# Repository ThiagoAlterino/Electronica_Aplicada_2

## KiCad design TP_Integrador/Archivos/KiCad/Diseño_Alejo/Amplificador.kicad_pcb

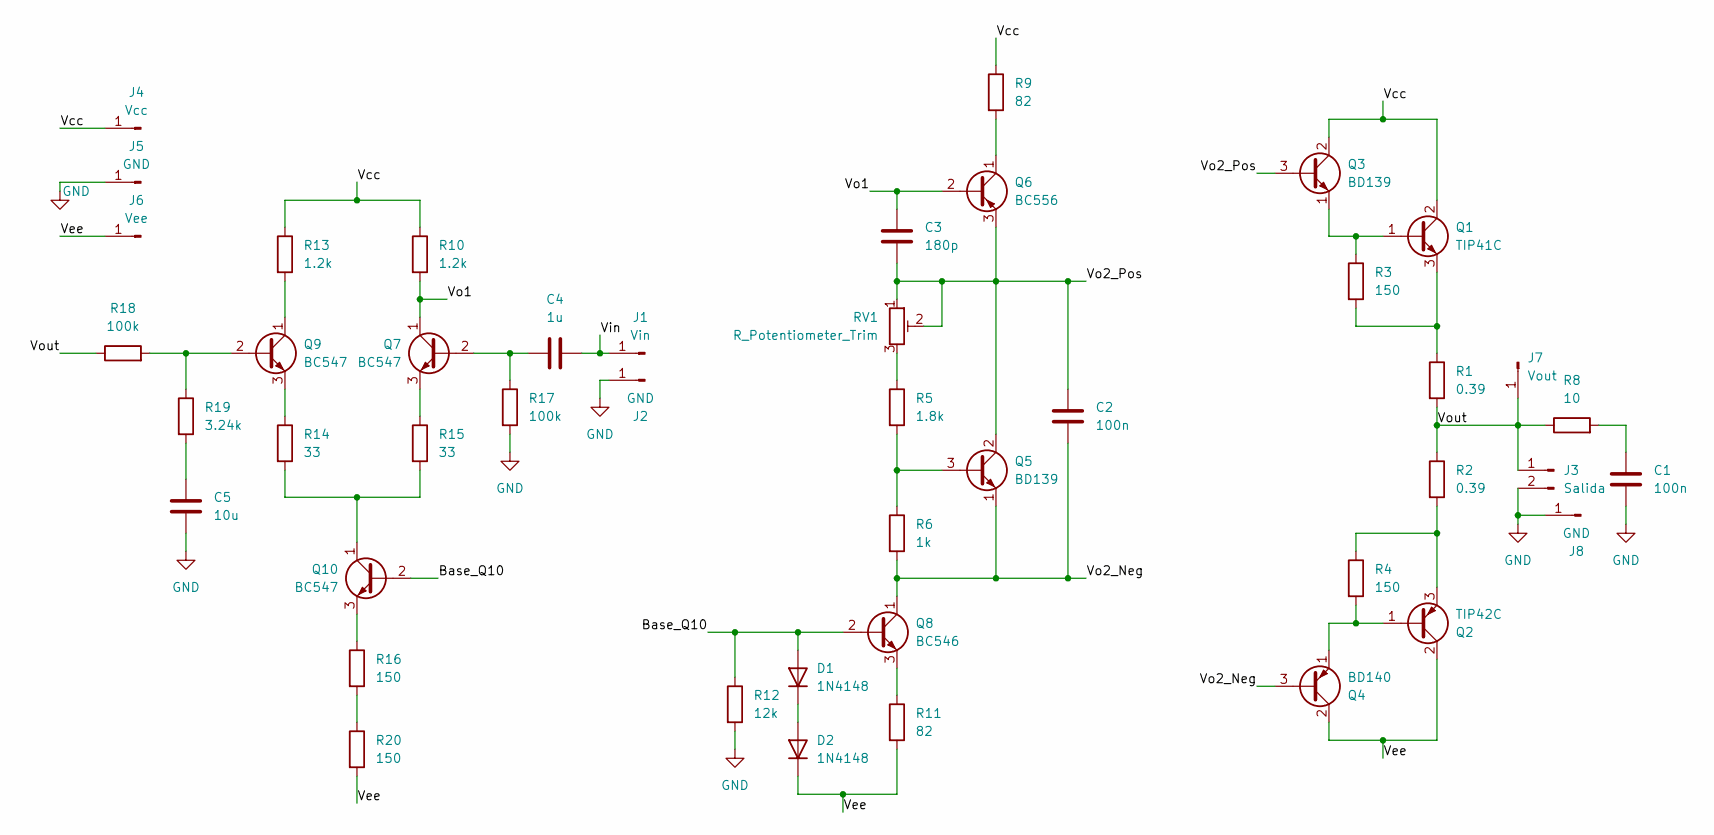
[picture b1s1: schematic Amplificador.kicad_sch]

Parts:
C1, C2: 100n; C_Rect_L7.2mm_W2.5mm_P5.00mm_FKS2_FKP2_MKS2_MKP2
C3: 180p; C_Disc_D5.0mm_W2.5mm_P5.00mm
C4: 1u; C_Rect_L10.3mm_W5.0mm_P7.50mm_MKS4
C5: 10u; CP_Radial_D5.0mm_P2.50mm
D1, D2: 1N4148; D_DO-35_SOD27_P7.62mm_Horizontal
J1: Vin; PinHeader_1x01_P2.54mm_Vertical
J2, J5, J8: GND; PinHeader_1x01_P2.54mm_Vertical
J3: Salida; TerminalBlock_Phoenix_MKDS-1,5-2-5.08_1x02_P5.08mm_Horizont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
J4: Vcc; PinHeader_1x01_P2.54mm_Vertical
J6: Vee; PinHeader_1x01_P2.54mm_Vertical
J7: Vout; PinHeader_1x01_P2.54mm_Vertical
Q1: TIP41C; TO-220-3_Vertical
Q2: TIP42C; TO-220-3_Vertical
Q3, Q5: BD139; TO-126-3_Vertical
Q4: BD140; TO-126-3_Vertical
Q6: BC556; TO-92_Inline
Q7, Q9, Q10: BC547; TO-92_Inline
Q8: BC546; TO-92_Inline
R1, R2: 0.39; R_Axial_DIN0414_L11.9mm_D4.5mm_P15.24mm_Horizontal
R3, R4, R16, R20: 150; R_Axial_DIN0207_L6.3mm_D2.5mm_P10.16mm_Horizontal
R5: 1.8k; R_Axial_DIN0207_L6.3mm_D2.5mm_P10.16mm_Horizontal
R6: 1k; R_Axial_DIN0207_L6.3mm_D2.5mm_P10.16mm_Horizontal
R8: 10; R_Axial_DIN0309_L9.0mm_D3.2mm_P12.70mm_Horizontal
R9, R11: 82; R_Axial_DIN0207_L6.3mm_D2.5mm_P10.16mm_Horizontal
R10, R13: 1.2k; R_Axial_DIN0207_L6.3mm_D2.5mm_P10.16mm_Horizontal
R12: 12k; R_Axial_DIN0207_L6.3mm_D2.5mm_P10.16mm_Horizontal
R14, R15: 33; R_Axial_DIN0207_L6.3mm_D2.5mm_P10.16mm_Horizontal
R17, R18: 100k; R_Axial_DIN0207_L6.3mm_D2.5mm_P10.16mm_Horizontal
R19: 3.24k; R_Axial_DIN0207_L6.3mm_D2.5mm_P10.16mm_Horizontal
RV1: R_Potentiometer_Trim; Potentiometer_Bourns_3296W_Vertical

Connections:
/Base_Q10: D1.2 (A), Q8.2 (B), Q10.2 (B), R12.1
/Vcc: J4.1 (Pin_1_1), Q1.2 (C), Q3.2 (C), R9.1, R10.1, R13.1
/Vee: D2.1 (K), J6.1 (Pin_1_1), Q2.2 (C), Q4.2 (C), R11.2, R20.2
/Vin: C4.2, J1.1 (Pin_1_1)
/Vo1: C3.1, Q6.2 (B), Q7.1 (C), R10.2
/Vo2_Neg: C2.2, Q4.3 (B), Q5.1 (E), Q8.1 (C), R6.2
/Vo2_Pos: C2.1, C3.2, Q3.3 (B), Q5.2 (C), Q6.3 (E), RV1.1, RV1.2
/Vout: J3.1, J7.1 (Pin_1_1), R1.2, R2.1, R8.1, R18.1
GND: C1.2, C5.2, J2.1 (Pin_1_1), J3.2, J5.1 (Pin_1_1), J8.1 (Pin_1_1), R12.2, R17.2
unnamed: C1.1, R8.2
unnamed: C5.1, R19.2
unnamed: D1.1 (K), D2.2 (A)
unnamed: Q1.1 (B), Q3.1 (E), R3.1
unnamed: Q1.3 (E), R1.1, R3.2
unnamed: Q2.1 (B), Q4.1 (E), R4.2
unnamed: Q2.3 (E), R2.2, R4.1
unnamed: Q5.3 (B), R5.2, R6.1
unnamed: Q6.1 (C), R9.2
unnamed: C4.1, Q7.2 (B), R17.1
unnamed: Q7.3 (E), R15.1
unnamed: Q8.3 (E), R11.1
unnamed: Q9.2 (B), R18.2, R19.1
unnamed: Q9.1 (C), R13.2
unnamed: Q9.3 (E), R14.1
unnamed: Q10.1 (C), R14.2, R15.2
unnamed: Q10.3 (E), R16.1
unnamed: R5.1, RV1.3
unnamed: R16.2, R20.1

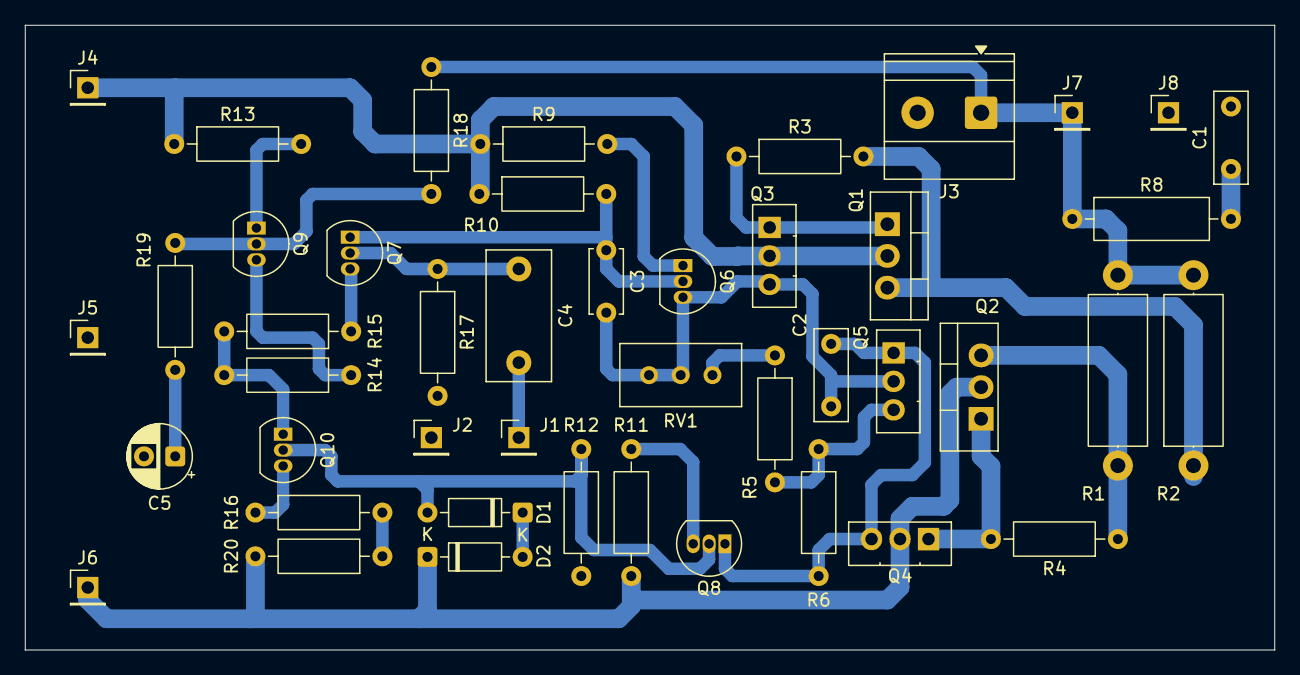
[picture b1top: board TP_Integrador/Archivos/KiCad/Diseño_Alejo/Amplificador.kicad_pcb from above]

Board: 2 copper layers, 100.0 x 50.0 mm, 45 parts (0 on the bottom side), 28 nets.

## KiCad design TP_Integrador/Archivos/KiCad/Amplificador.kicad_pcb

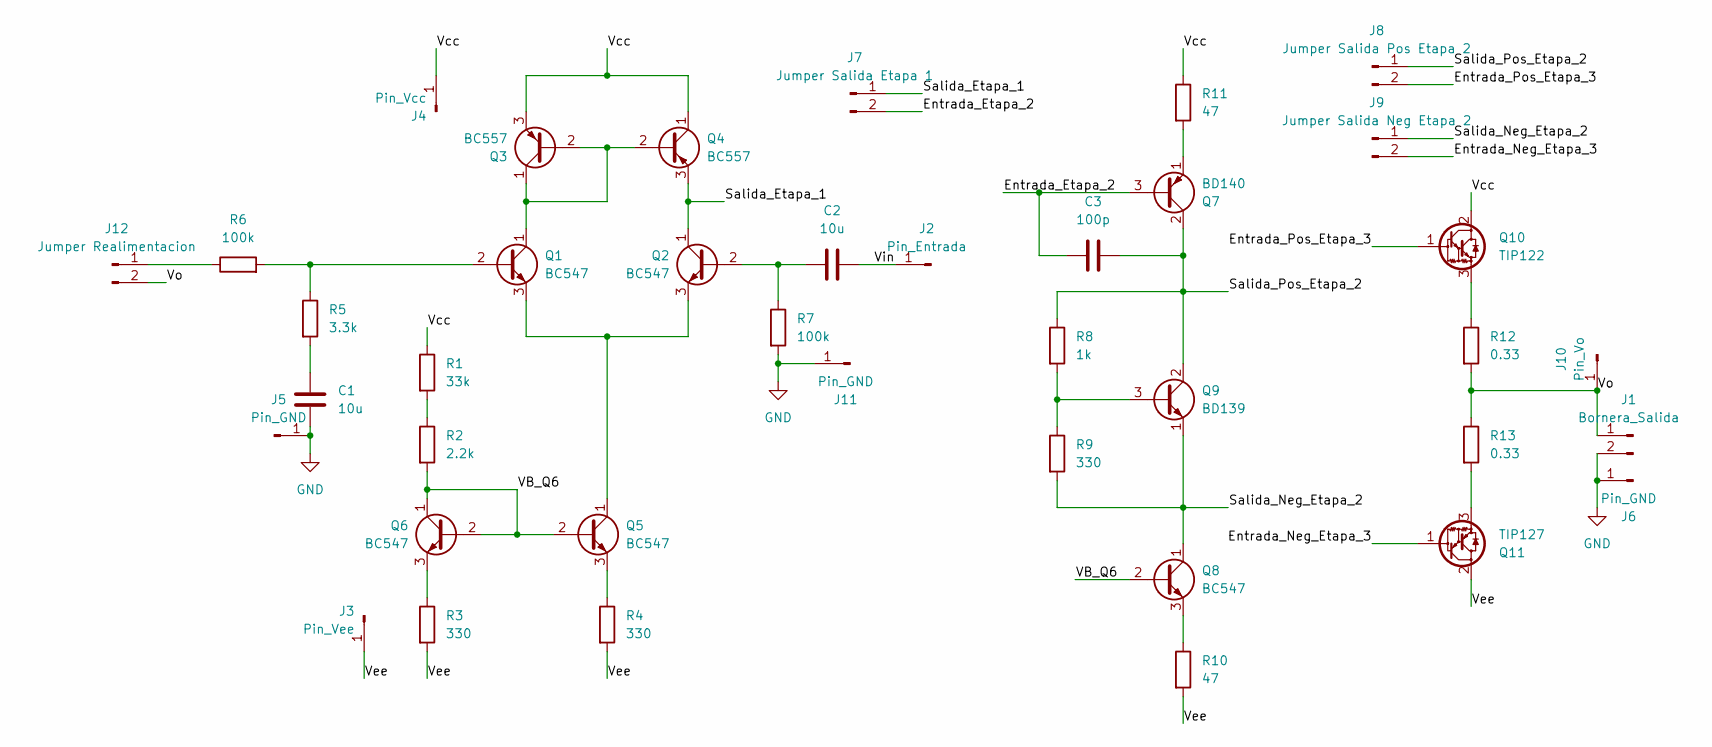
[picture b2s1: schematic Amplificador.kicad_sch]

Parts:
C1, C2: 10u; CP_Radial_D5.0mm_P2.50mm
C3: 100p; C_Disc_D10.0mm_W2.5mm_P5.00mm
J1: Bornera_Salida; TerminalBlock_Phoenix_MKDS-1,5-2-5.08_1x02_P5.08mm_Horizont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
J2: Pin_Entrada; PinHeader_1x01_P2.54mm_Vertical
J3: Pin_Vee; PinHeader_1x01_P2.54mm_Vertical
J4: Pin_Vcc; PinHeader_1x01_P2.54mm_Vertical
J5, J6, J11: Pin_GND; PinHeader_1x01_P2.54mm_Vertical
J7: Jumper Salida Etapa 1; PinHeader_1x02_P2.54mm_Vertical
J8: Jumper Salida Pos Etapa 2; PinHeader_1x02_P2.54mm_Vertical
J9: Jumper Salida Neg Etapa 2; PinHeader_1x02_P2.54mm_Vertical
J10: Pin_Vo; PinHeader_1x01_P2.54mm_Vertical
J12: Jumper Realimentacion; PinHeader_1x02_P2.54mm_Vertical
Q1, Q2, Q5, Q6, Q8: BC547; TO-92_Inline
Q3, Q4: BC557; TO-92_Inline
Q7: BD140; TO-126-3_Vertical
Q9: BD139; TO-126-3_Vertical
Q10: TIP122; TO-220-3_Vertical
Q11: TIP127; TO-220-3_Vertical
R1: 33k; R_Axial_DIN0207_L6.3mm_D2.5mm_P10.16mm_Horizontal
R2: 2.2k; R_Axial_DIN0207_L6.3mm_D2.5mm_P10.16mm_Horizontal
R3, R4, R9: 330; R_Axial_DIN0207_L6.3mm_D2.5mm_P10.16mm_Horizontal
R5: 3.3k; R_Axial_DIN0207_L6.3mm_D2.5mm_P10.16mm_Horizontal
R6, R7: 100k; R_Axial_DIN0207_L6.3mm_D2.5mm_P10.16mm_Horizontal
R8: 1k; R_Axial_DIN0207_L6.3mm_D2.5mm_P10.16mm_Horizontal
R10, R11: 47; R_Axial_DIN0207_L6.3mm_D2.5mm_P10.16mm_Horizontal
R12, R13: 0.33; R_Axial_Power_L25.0mm_W6.4mm_P27.94mm

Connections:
/Entrada_Etapa_2: C3.1, J7.2, Q7.3 (B)
/Entrada_Neg_Etapa_3: J9.2, Q11.1 (B)
/Entrada_Pos_Etapa_3: J8.2, Q10.1 (B)
/Salida_Etapa_1: J7.1, Q2.1 (C), Q4.3 (E)
/Salida_Neg_Etapa_2: J9.1, Q8.1 (C), Q9.1 (E), R9.2
/Salida_Pos_Etapa_2: C3.2, J8.1, Q7.2 (C), Q9.2 (C), R8.1
/VB_Q6: Q5.2 (B), Q6.1 (C), Q6.2 (B), Q8.2 (B), R2.2
/Vcc: J4.1 (Pin_1_1), Q3.3 (E), Q4.1 (C), Q10.2 (C), R1.1, R11.1
/Vee: J3.1 (Pin_1_1), Q11.2 (C), R3.2, R4.2, R10.2
/Vin: C2.2, J2.1 (Pin_1_1)
/Vo: J1.1, J10.1 (Pin_1_1), J12.2, R12.2, R13.1
GND: C1.2, J1.2, J5.1 (Pin_1_1), J6.1 (Pin_1_1), J11.1 (Pin_1_1), R7.2
unnamed: C1.1, R5.2
unnamed: J12.1, R6.1
unnamed: Q1.2 (B), R5.1, R6.2
unnamed: Q1.1 (C), Q3.1 (C), Q3.2 (B), Q4.2 (B)
unnamed: Q1.3 (E), Q2.3 (E), Q5.1 (C)
unnamed: C2.1, Q2.2 (B), R7.1
unnamed: Q5.3 (E), R4.1
unnamed: Q6.3 (E), R3.1
unnamed: Q7.1 (E), R11.2
unnamed: Q8.3 (E), R10.1
unnamed: Q9.3 (B), R8.2, R9.1
unnamed: Q10.3 (E), R12.1
unnamed: Q11.3 (E), R13.2
unnamed: R1.2, R2.1

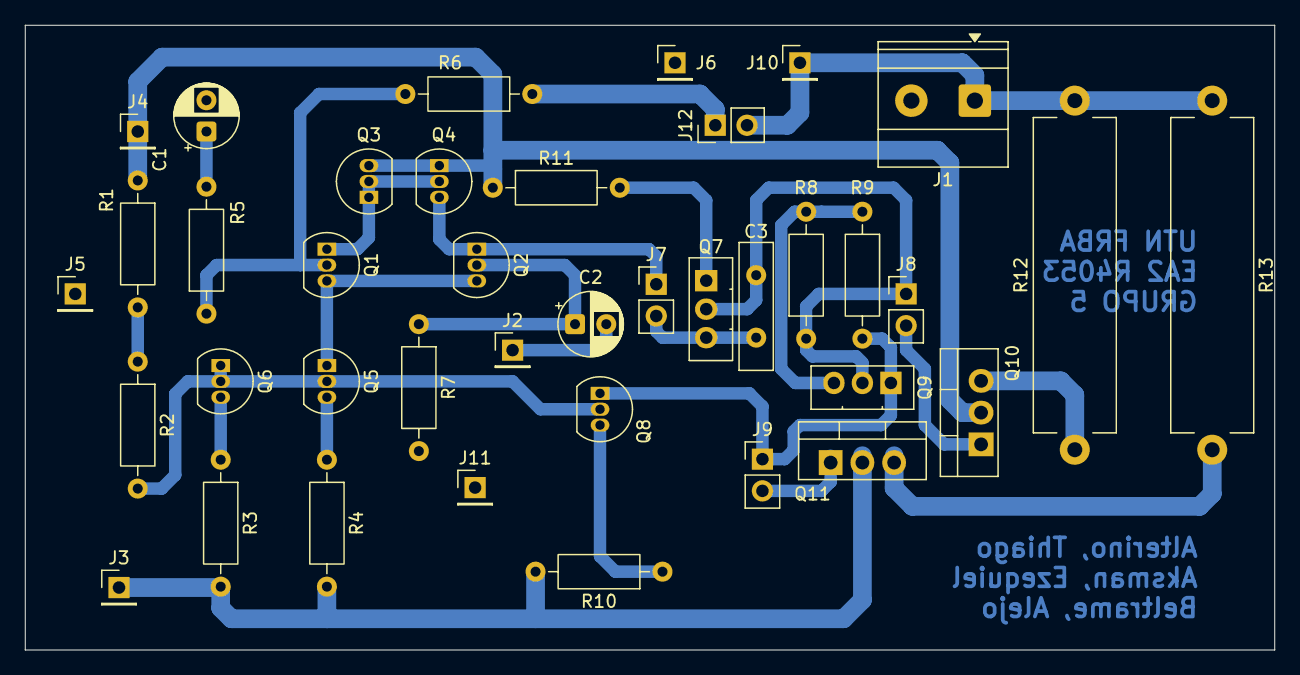
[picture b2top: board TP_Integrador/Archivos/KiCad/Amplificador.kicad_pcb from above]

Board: 2 copper layers, 100.0 x 50.0 mm, 39 parts (0 on the bottom side), 26 nets.
